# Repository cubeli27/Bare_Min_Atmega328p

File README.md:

# Bare_Min_Atmega328p
PCB designed for available in-house parts. With my main goal to test the procces of ordering from a fab house, see the outcome, as well as lab capabilities with relatively tiny components, and USB to UART.

# Assembly

Silkscreen is simplified for hand assembly hence the minimum amount of different values and the same names for many parts;
 ```ignore
 | Resistor |  Capacitor   | Inductor    |    LED                  |
 |----------|--------------|-------------|-------------------------|
 | R1 = 1k  | C1 = 100nF   |  L1 = 10uH  | PWR = White             |
 | R2 = 470 | C2 = 22pF    |             | R/G/B = Red/Green/Blue  |
 | R3 = 10k | C3 = 10uF    |             | RX/TX = Orange          |

 ```

Tip: 
R1 next to the PWR led should be more than 1k unless you want it to always be too bright, I recommend 1k8 or 2k2.

# Programming
1. Open in Arduino IDE File/Examples/11.ArduinoISP/ArduinoISP.
2. Uncomment line 81 (// #define USE_OLD_STYLE_WIRING).

3. Upload the code to your Arduino Uno with Board: Arduino Uno, Programmer: AVRISP mkII.
4. Connect Arduino Uno with the custom board like so:
 ```ignore
 | Uno      |  Custom Board| 
 |----------|--------------|
 | 10       | RESET        |  
 | 11       | MOSI         | 
 | 12       | MISO         |  
 | 13       | SCK          |
 | 5v       | 5v           |
 | GND      | GND          |
 ```

5. Burning the bootloader steps. In Tools set Board: Arduino Duemilanove or Diecimila, Programmer: Arduino as ISP, then click Burn Bootloader.

6. You should see "Done Burning Bootloader". Now you're set and can unplug your jumper wires and store your Arduino Uno you won't need it anymore.

7. Connect your custom board to your PC through a USB cable.
8. In order to upload any code just select in Tools Board: Arduino Duemilanove or Diecimila, Programmer: AVRISP mkII, and click Upload (arrow pointing right). You should see the orange LEDs flashing.
9. If you want to start with the blink sketch make sure to use pins 5,6 or 7 because built-in LED's are on those pins.
 ```ignore
 | PIN      |  LED        | 
 |----------|-------------|
 | PD7      | RED         |  
 | PD6      | GREEN       | 
 | PD5      | BLUE        |  
 ```

# *Disclaimer*

This board has no defined purpose it was made for testing the ordering process, the lab assembly capabilities, and USB to UART. 
Additionally, it was designed for the preexisting available components that were lying around the lab. Hence the part selection is suboptimal.
And looking back the design also isn't great, but this being the first board I ever ordered externally I'm super happy with the results and with what I learned.

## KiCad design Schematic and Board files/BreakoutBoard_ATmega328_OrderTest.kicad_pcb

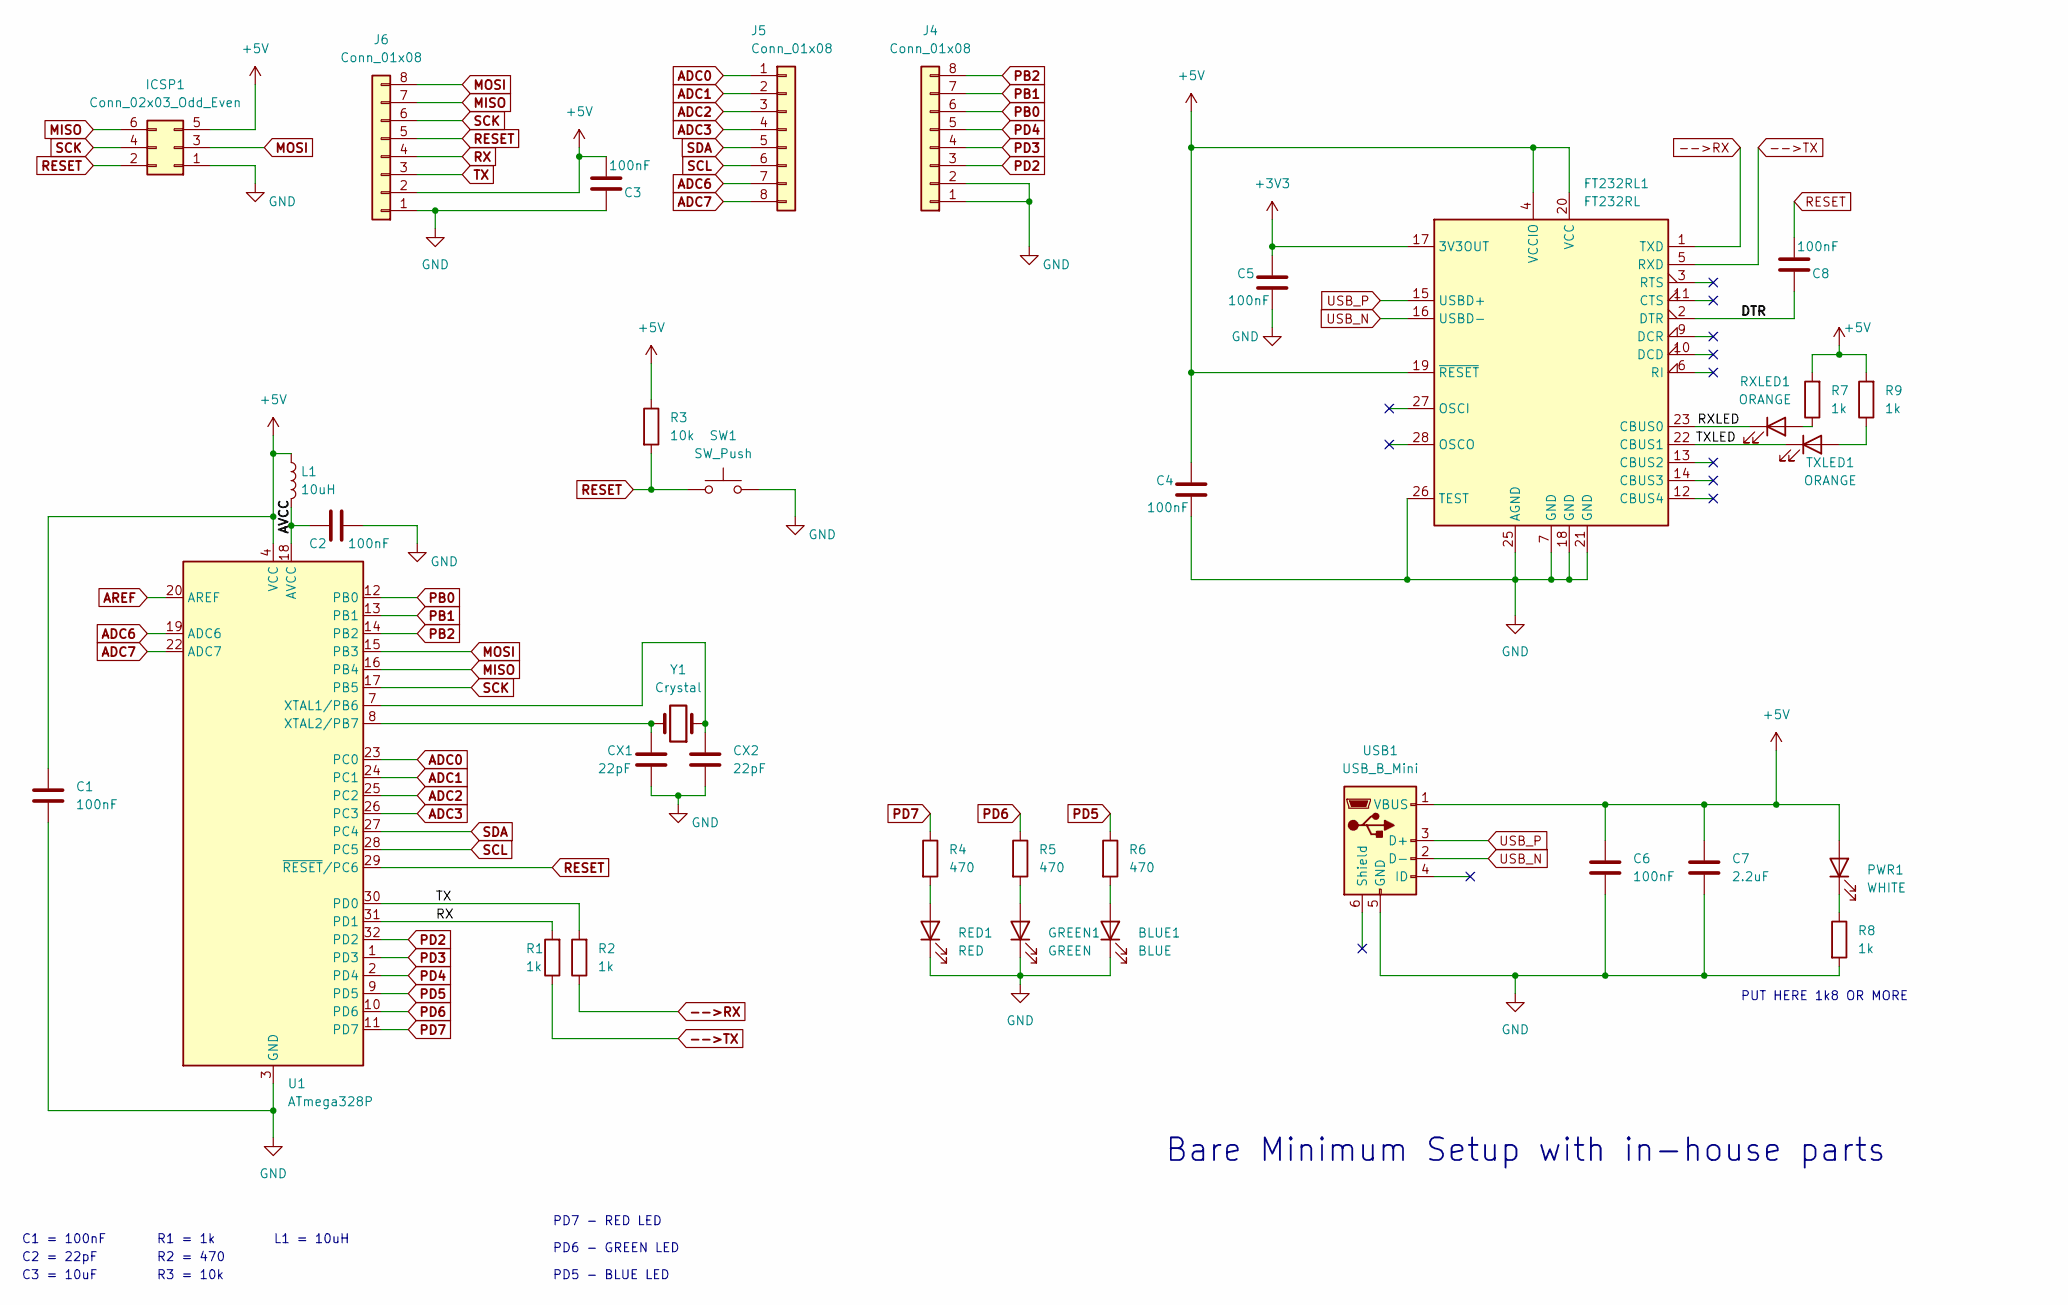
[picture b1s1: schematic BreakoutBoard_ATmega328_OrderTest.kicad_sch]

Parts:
BLUE1: BLUE; LED_1206_3216Metric
C1, C2, C3, C4, C5, C6, C8: 100nF; C_1206_3216Metric
C7: 2.2uF; C_1206_3216Metric
CX1, CX2: 22pF; C_0805_2012Metric
FT232RL1: FT232RL; SSOP-28_5.3x10.2mm_P0.65mm
GREEN1: GREEN; LED_1206_3216Metric
ICSP1: Conn_02x03_Odd_Even; PinHeader_2x03_P2.54mm_Vertical
J4, J5, J6: Conn_01x08
L1: 10uH; L_0805_2012Metric
PWR1: WHITE; LED_1206_3216Metric
R1, R2, R7, R8, R9: 1k; R_1206_3216Metric
R3: 10k; R_1206_3216Metric
R4, R5, R6: 470; R_1206_3216Metric
RED1: RED; LED_1206_3216Metric
RXLED1: ORANGE; LED_1206_3216Metric
SW1: SW_Push; SW_SPST_TL3342
TXLED1: ORANGE; LED_1206_3216Metric
U1: ATmega328P; TQFP-32_7x7mm_P0.8mm
USB1: USB_B_Mini; USB_Mini-B_Wuerth_65100516121_Horizontal
Y1: Crystal; Crystal_SMD_HC49-SD

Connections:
+3V3: C5.1, FT232RL1.17 (3V3OUT)
+5V: C1.1, C3.2, C4.1, C6.1, C7.1, FT232RL1.4 (VCCIO), FT232RL1.19 (~RESET), FT232RL1.20 (VCC), ICSP1.5, J6.2, L1.1, PWR1.2 (A), R3.1, R7.2, R9.2, U1.4 (VCC), U1.6 (VCC), USB1.1 (VBUS); also elsewhere on the board
-->RX: FT232RL1.1 (TXD), R2.1
-->TX: FT232RL1.5 (RXD), R1.1
/AVCC: C2.1, L1.2, U1.18 (AVCC)
/DTR: C8.1, FT232RL1.2 (DTR)
/RXLED: FT232RL1.23 (CBUS0), RXLED1.1 (K)
/TXLED: FT232RL1.22 (CBUS1), TXLED1.1 (K)
ADC0: J5.1, U1.23 (PC0); also elsewhere on the board
ADC1: J5.2, U1.24 (PC1); also elsewhere on the board
ADC2: J5.3, U1.25 (PC2); also elsewhere on the board
ADC3: J5.4, U1.26 (PC3); also elsewhere on the board
ADC6: J5.7, U1.19 (ADC6); also elsewhere on the board
ADC7: J5.8, U1.22 (ADC7); also elsewhere on the board
AREF: U1.20 (AREF)
GND: BLUE1.1 (K), C1.2, C2.2, C3.1, C4.2, C5.2, C6.2, C7.2, CX1.2, CX2.2, FT232RL1.7 (GND), FT232RL1.18 (GND), FT232RL1.21 (GND), FT232RL1.25 (AGND), FT232RL1.26 (TEST), GREEN1.1 (K), ICSP1.1, J4.1, J4.2, J6.1, R8.2, RED1.1 (K), SW1.2, U1.3 (GND), U1.5 (GND), U1.21 (GND), USB1.5 (GND); also elsewhere on the board
MISO: ICSP1.6, J6.7, U1.16 (PB4); also elsewhere on the board
MOSI: ICSP1.3, J6.8, U1.15 (PB3); also elsewhere on the board
unnamed: BLUE1.2 (A), R6.2
unnamed: GREEN1.2 (A), R5.2
unnamed: PWR1.1 (K), R8.1
unnamed: R4.2, RED1.2 (A)
unnamed: R7.1, RXLED1.2 (A)
unnamed: R9.1, TXLED1.2 (A)
unnamed: CX2.1, U1.7 (XTAL1/PB6), Y1.1
unnamed: CX1.1, U1.8 (XTAL2/PB7), Y1.2
PB0: J4.6, U1.12 (PB0); also elsewhere on the board
PB1: J4.7, U1.13 (PB1); also elsewhere on the board
PB2: J4.8, U1.14 (PB2); also elsewhere on the board
PD2: J4.3, U1.32 (PD2); also elsewhere on the board
PD3: J4.4, U1.1 (PD3); also elsewhere on the board
PD4: J4.5, U1.2 (PD4); also elsewhere on the board
PD5: R6.1, U1.9 (PD5)
PD6: R5.1, U1.10 (PD6)
PD7: R4.1, U1.11 (PD7)
RESET: C8.2, ICSP1.2, J6.5, R3.2, SW1.1, U1.29 (~RESET/PC6); also elsewhere on the board
RX: R1.2, U1.31 (PD1); also elsewhere on the board
SCK: ICSP1.4, J6.6, U1.17 (PB5); also elsewhere on the board
SCL: J5.6, U1.28 (PC5); also elsewhere on the board
SDA: J5.5, U1.27 (PC4); also elsewhere on the board
TX: R2.2, U1.30 (PD0); also elsewhere on the board
USB_N: FT232RL1.16 (USBD-), USB1.2 (D-)
USB_P: FT232RL1.15 (USBD+), USB1.3 (D+)

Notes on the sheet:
R2 = 470
C3 = 10uF
PUT HERE 1k8 OR MORE
C1 = 100nF
R1 = 1k
PD5 - BLUE LED
PD6 - GREEN LED
C2 = 22pF
Bare Minimum Setup with in-house parts
R3 = 10k
PD7 - RED LED
L1 = 10uH

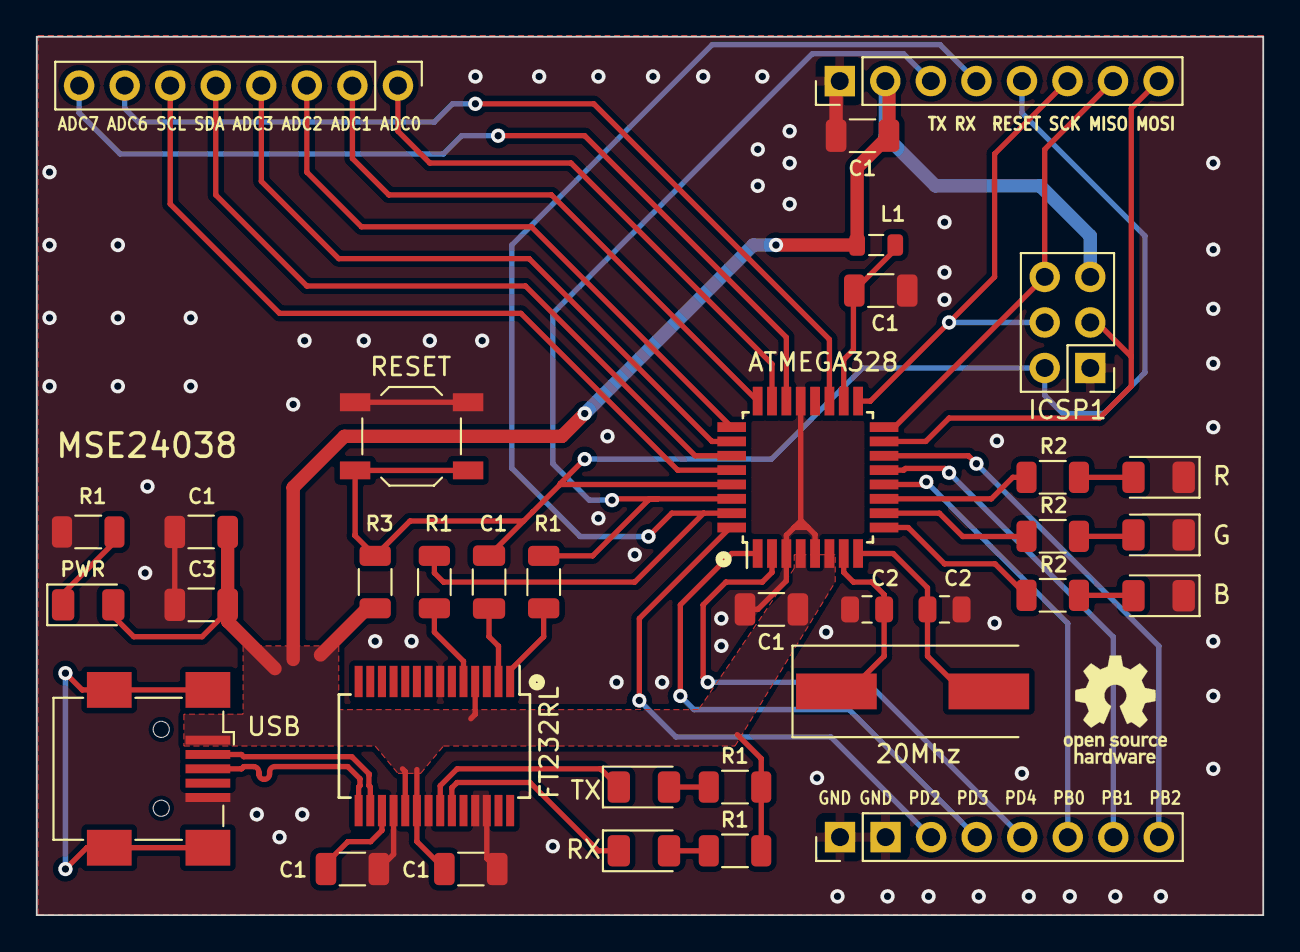
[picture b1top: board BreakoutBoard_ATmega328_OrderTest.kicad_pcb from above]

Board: 2 copper layers, 68.4 x 49.0 mm, 35 parts (0 on the bottom side), 42 nets.

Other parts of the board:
J1, J2, J3: Conn_01x08_Socket; PinHeader_1x08_P2.54mm_Vertical

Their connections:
+5V: J1.2; also elsewhere on the board
ADC0: J2.1; also elsewhere on the board
ADC1: J2.2; also elsewhere on the board
ADC2: J2.3; also elsewhere on the board
ADC3: J2.4; also elsewhere on the board
ADC6: J2.7; also elsewhere on the board
ADC7: J2.8; also elsewhere on the board
GND: J1.1, J3.1, J3.2; also elsewhere on the board
MISO: J1.7; also elsewhere on the board
MOSI: J1.8; also elsewhere on the board
PB0: J3.6; also elsewhere on the board
PB1: J3.7; also elsewhere on the board
PB2: J3.8; also elsewhere on the board
PD2: J3.3; also elsewhere on the board
PD3: J3.4; also elsewhere on the board
PD4: J3.5; also elsewhere on the board
RESET: J1.5; also elsewhere on the board
RX: J1.4; also elsewhere on the board
SCK: J1.6; also elsewhere on the board
SCL: J2.6; also elsewhere on the board
SDA: J2.5; also elsewhere on the board
TX: J1.3; also elsewhere on the board

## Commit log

2023-11-08 Create LICENSE
